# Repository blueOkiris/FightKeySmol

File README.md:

# Fight Key Smol

## Description

I made a [hitbox for myself](https://hackaday.io/project/185796-fight-key-wide) a while back that's big and has an enclosure and all that good stuff and cost me maybe $80 to make.

However, lately I've been seeing people pay well over $100 for something that should be maybe $50 max, so I'm redesigning that to fit the style people want, so there's a cheap alternative.

Now yes, you're paying for quality with the others. This doesn't come with an enclosure, and it's DIY; it's minimal, but for some people, that's worth not dropping >= $100. It's an option. That's all

So, this project aims to be a tiny, inexpensive, DIY, keyboard-based fighting-game controller.

## Software

The software included in the repo and releases is a pre-built version of the [GP2040-CE](https://github.com/OpenStickCommunity/GP2040-CE) firmware.

For version 1, there is a custom version due to Start and Select being switched. For version 2, this is not the case, and the stock software can be used.

## Parts

The only thing you need to source yourself are the key caps. You can get a cheap set for $2 on [Aliexpress](CapLink).

Beyond that, you'll want to use [Jlcpcb](https://jlcpcb.com) to order the board and use automatic assembly. This will place all the internals as well as the switches into the PCB and ship it to you.

Cost comes out to:

| Part                                              | Cost |
|:-------------------------------------------------:|:----:|
| PCB and Assembly                                  | $22  |
| PCB Shipping (Choose Global Standard for cheaper) | $10  |
| Key Caps                                          | $2   |
| Total                                             | $34  |

[CapLink]: https://www.aliexpress.us/item/3256803462871478.html?spm=a2g0o.productlist.main.15.fd98sl21sl21Ub&algo_pvid=9ed2559f-ab14-4ea8-b05c-93050b38520c&algo_exp_id=9ed2559f-ab14-4ea8-b05c-93050b38520c-7&pdp_npi=3%40dis%21USD%211.5%211.12%21%21%21%21%21%4021224e9b16806567975486574d074d%2112000026645768333%21sea%21US%210&curPageLogUid=vViLogs9j2Z2 "Aliexpress"

## Subdirectories

- pcb - Fight Key Smol KiCAD PCB project
- pics - Pics used for the README

## Ordering and Programming

1. Go to JLCPCB and click on "Instant Quote"
   
2. Click "Upload" and upload the "FightKeySmol-Gerber.zip" file from the GitHub Releases. You don't need to mess with any options here.
3. Scroll down to "PCB Assembly" and enable it. Select just one and click Submit
   
4. Click Next and then upload the "pcb/parts/BOM.xls" for the BOM and "pcb/parts/FightKey-CPL.xlsx" for the CPL. Then click process.
   
5. Click to continue on the next page, and proceed to ordering the boards.
6. Once you have the board, you need to program it. You don't need to rebuild the code or anything.
   1. Press the pico's button down and plug it in to make it show up as a drive
   2. Copy the .uf2 file in the repo to the drive. It will unmount and program and auto-remount as a controller
   
7. Enjoy!

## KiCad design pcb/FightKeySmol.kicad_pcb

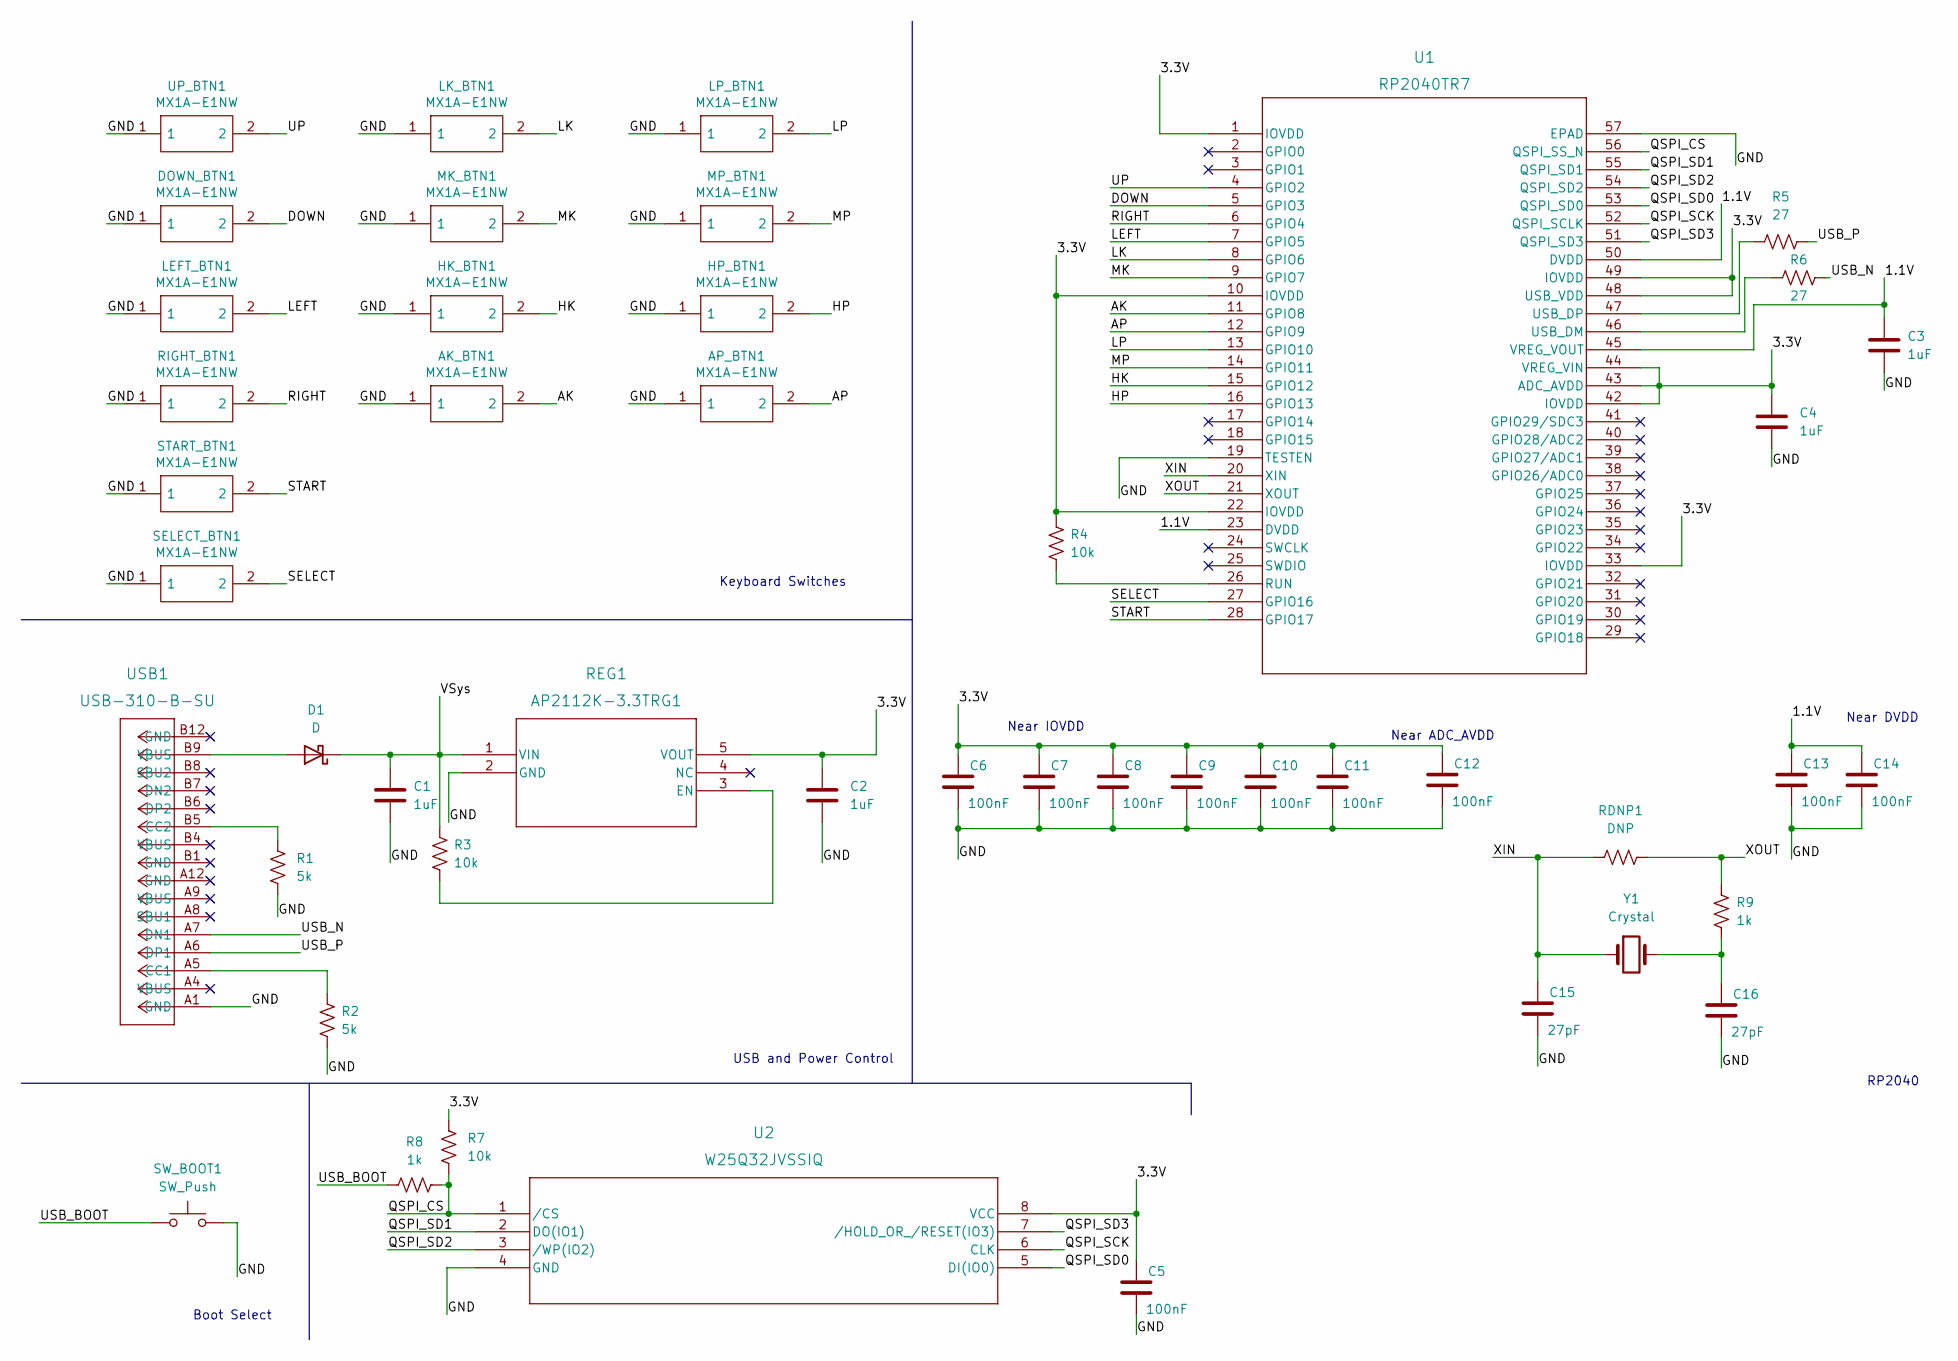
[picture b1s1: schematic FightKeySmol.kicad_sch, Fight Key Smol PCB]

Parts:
AK_BTN1: MX1A-E1NW; MX1AE1NW; Mouser Part Number 540-MX1A-E1NW
AP_BTN1: MX1A-E1NW; MX1AE1NW; Mouser Part Number 540-MX1A-E1NW
C1, C2, C3, C4: 1uF; C_0201_0603Metric
C5, C6, C7, C8, C9, C10, C11, C12, C13, C14: 100nF; C_0201_0603Metric
C15, C16: 27pF; C_0201_0603Metric
D1: D; D_SOD-323
DOWN_BTN1: MX1A-E1NW; MX1AE1NW; Mouser Part Number 540-MX1A-E1NW
HK_BTN1: MX1A-E1NW; MX1AE1NW; Mouser Part Number 540-MX1A-E1NW
HP_BTN1: MX1A-E1NW; MX1AE1NW; Mouser Part Number 540-MX1A-E1NW
LEFT_BTN1: MX1A-E1NW; MX1AE1NW; Mouser Part Number 540-MX1A-E1NW
LK_BTN1: MX1A-E1NW; MX1AE1NW; Mouser Part Number 540-MX1A-E1NW
LP_BTN1: MX1A-E1NW; MX1AE1NW; Mouser Part Number 540-MX1A-E1NW
MK_BTN1: MX1A-E1NW; MX1AE1NW; Mouser Part Number 540-MX1A-E1NW
MP_BTN1: MX1A-E1NW; MX1AE1NW; Mouser Part Number 540-MX1A-E1NW
R1, R2: 5k; R_0805_2012Metric
R3, R4, R7: 10k; R_0201_0603Metric
R5, R6: 27; R_0201_0603Metric
R8, R9: 1k; R_0201_0603Metric
RDNP1: DNP; R_0201_0603Metric
REG1: AP2112K-3.3TRG1; SOT_RG1_DIO
RIGHT_BTN1: MX1A-E1NW; MX1AE1NW; Mouser Part Number 540-MX1A-E1NW
SELECT_BTN1: MX1A-E1NW; MX1AE1NW; Mouser Part Number 540-MX1A-E1NW
START_BTN1: MX1A-E1NW; MX1AE1NW; Mouser Part Number 540-MX1A-E1NW
SW_BOOT1: SW_Push; SW_SPST_PTS645
U1: RP2040TR7; RP2040TR7_RPI
U2: W25Q32JVSSIQ; SOIC-8_5P28X5P28_WIN
UP_BTN1: MX1A-E1NW; MX1AE1NW; Mouser Part Number 540-MX1A-E1NW
USB1: USB-310-B-SU; CONN_USB-310-B-SU_HYA
Y1: Crystal; Crystal_SMD_HC49-SD

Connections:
/1.1V: C3.1, C13.1, C14.1, U1.23 (DVDD), U1.45 (VREG_VOUT), U1.50 (DVDD)
/3.3V: C2.1, C4.1, C5.1, C6.1, C7.1, C8.1, C9.1, C10.1, C11.1, C12.1, R4.1, R7.1, REG1.5 (VOUT), U1.1 (IOVDD), U1.10 (IOVDD), U1.22 (IOVDD), U1.33 (IOVDD), U1.42 (IOVDD), U1.43 (ADC_AVDD), U1.44 (VREG_VIN), U1.48 (USB_VDD), U1.49 (IOVDD), U2.8 (VCC)
/AK: AK_BTN1.2, U1.11 (GPIO8)
/AP: AP_BTN1.2, U1.12 (GPIO9)
/DOWN: DOWN_BTN1.2, U1.5 (GPIO3)
/GND: AK_BTN1.1, AP_BTN1.1, C1.2, C2.2, C3.2, C4.2, C5.2, C6.2, C7.2, C8.2, C9.2, C10.2, C11.2, C12.2, C13.2, C14.2, C15.2, C16.2, DOWN_BTN1.1, HK_BTN1.1, HP_BTN1.1, LEFT_BTN1.1, LK_BTN1.1, LP_BTN1.1, MK_BTN1.1, MP_BTN1.1, R1.2, R2.2, REG1.2 (GND), RIGHT_BTN1.1, SELECT_BTN1.1, START_BTN1.1, SW_BOOT1.2, U1.19 (TESTEN), U1.57 (EPAD), U2.4 (GND), UP_BTN1.1, USB1.A1 (GND)
/HK: HK_BTN1.2, U1.15 (GPIO12)
/HP: HP_BTN1.2, U1.16 (GPIO13)
/LEFT: LEFT_BTN1.2, U1.7 (GPIO5)
/LK: LK_BTN1.2, U1.8 (GPIO6)
/LP: LP_BTN1.2, U1.13 (GPIO10)
/MK: MK_BTN1.2, U1.9 (GPIO7)
/MP: MP_BTN1.2, U1.14 (GPIO11)
/QSPI_CS: R7.2, R8.2, U1.56 (QSPI_SS_N), U2.1 (/CS)
/QSPI_SCK: U1.52 (QSPI_SCLK), U2.6 (CLK)
/QSPI_SD0: U1.53 (QSPI_SD0), U2.5 (DI(IO0))
/QSPI_SD1: U1.55 (QSPI_SD1), U2.2 (DO(IO1))
/QSPI_SD2: U1.54 (QSPI_SD2), U2.3 (/WP(IO2))
/QSPI_SD3: U1.51 (QSPI_SD3), U2.7 (/HOLD_OR_/RESET(IO3))
/RIGHT: RIGHT_BTN1.2, U1.6 (GPIO4)
/SELECT: SELECT_BTN1.2, U1.27 (GPIO16)
/START: START_BTN1.2, U1.28 (GPIO17)
/UP: U1.4 (GPIO2), UP_BTN1.2
/USB_BOOT: R8.1, SW_BOOT1.1
/USB_N: R6.1, USB1.A7 (DN1)
/USB_P: R5.2, USB1.A6 (DP1)
/VSys: C1.1, D1.1 (K), R3.1, REG1.1 (VIN)
/XIN: C15.1, RDNP1.1, U1.20 (XIN), Y1.1
/XOUT: R9.2, RDNP1.2, U1.21 (XOUT)
unnamed: C16.1, R9.1, Y1.2
unnamed: D1.2 (A), USB1.B9 (VBUS)
unnamed: R1.1, USB1.B5 (CC2)
unnamed: R2.1, USB1.A5 (CC1)
unnamed: R3.2, REG1.3 (EN)
unnamed: R4.2, U1.26 (RUN)
unnamed: R5.1, U1.47 (USB_DP)
unnamed: R6.2, U1.46 (USB_DM)

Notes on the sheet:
Near ADC_AVDD
Boot Select
Near DVDD
Near IOVDD
RP2040
USB and Power Control
Keyboard Switches

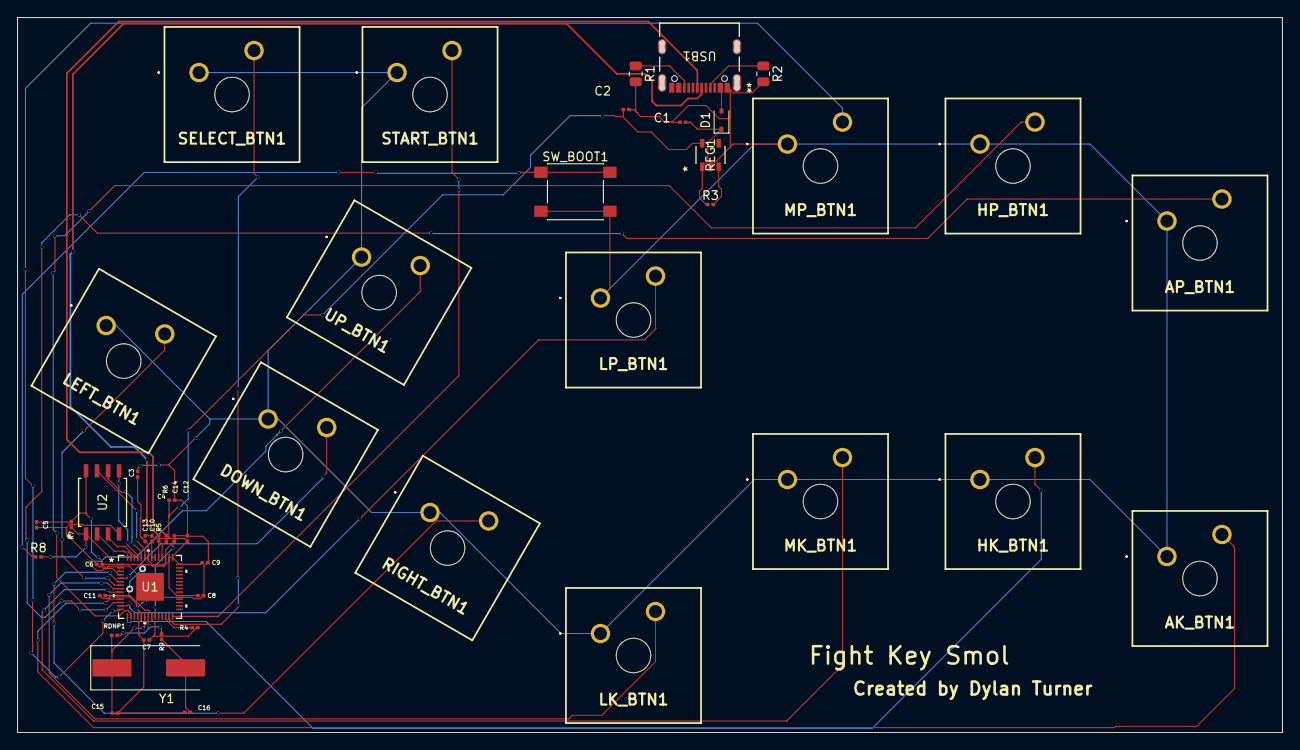
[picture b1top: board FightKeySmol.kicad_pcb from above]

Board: 2 copper layers, 146.1 x 82.6 mm, 47 parts (0 on the bottom side), 37 nets.

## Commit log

2023-04-05 pcb: added from fightkey-wide proj
2023-04-05 README: initial template with basic motivations
2023-04-05 README: update tag line
2023-04-05 GP2040-CE: added code for programming
2023-04-05 README: add disclaimer about project state
2023-04-05 LICENSE: added MIT (what GP2040-CE uses)
    I don't care all that much, since I'm not doing any coding
2023-04-05 gitignore: ignore KiCAD output/backup files
2023-04-05 README: switches link points to cheap knockoffs
    No need for fancy ones since this is a low-end device
2023-04-05 kicad_sch: redesigned to use input_pullup
    This is the standard for GP2040 style sticks.
    Use PICO_BOARD_CONFIG_H_
2023-04-05 kicad_sch: added second ground on other side
2023-04-05 kicad_pcb: updated for schem and new tiny design
2023-04-05 kicad_pcb: updated for new design
2023-04-05 README: note programming in build steps
2023-04-05 jlcpcb-order: pic of options
2023-04-05 README: update cost
2023-04-05 README: found cheaper alternatives
2023-04-05 README: update expected
2023-04-14 GP2040-CE_0.6.2_Pico: added fk program
2023-04-14 GP2040-CE_0.6.2_Pico: switched start/select
    I mixed up S1 and S2 when designing the PCB
2023-04-14 pics/: added build pics
2023-04-14 README: updated build steps for "release"
    I.e. initial version is ready, and I can fill in the build steps
2023-04-14 GP2040-CE: switched to custom version
2023-04-14 README: fix typo
2023-04-14 README: update links and costs
2023-04-14 README: noted use of hot glue as feet alternative
2023-04-14 README: noted pics folder
2023-04-14 README: fixed cost note
2023-04-14 kicad_pcb: shrink board; switch start sel
2023-04-14 kicad_sch: switch start/sel
2023-04-14 gitmodules: remove uneeded fork of GP2040
2023-04-14 GP2040-CE: replaced with stock
2023-04-14 kicad_sch: delete pico
2023-04-14 kicad_pcb: delete pico, rm traces, shrink board
2023-04-14 README: add info on GP2040-CE
2023-04-14 USB-310-B: usb-C connector for custom board
2023-04-14 BOM: initialized BOM with USB-C
2023-04-14 pico-soldering: removed
    Built-in board with through hole, but not pico
2023-04-14 README: add flash chip to cost
2023-04-14 ul_W25Q32JVSSIQ: flash chip added
2023-04-14 BOM: add voltage regulator
2023-04-14 ul_AP2112K-3.3TRG1: voltage regulator
2023-04-14 BOM: resistors for USB-C power
2023-04-14 fp-lib-table: add parts to project symbol lib
2023-04-14 sym-lib-table: add custom parts to sym lib
2023-04-14 fp-info-cache: updated resistor footprints
2023-04-14 kicad_sch: implement USB/Power circuit
2023-04-14 kicad_pcb: place and route parts for USB/Power
2023-04-14 kicad_pro: new parts
2023-04-14 BOM: updated for power circuitry
2023-04-15 ul_RP2040TR7: 2040 symbols/footprint library
2023-04-15 fp-lib-table: add 2040 library
2023-04-15 sym-lib-table: add 2040 symbol lib
2023-04-15 kicad_sch: set up 2040 circuit
2023-04-15 BOM: completed (unless errors)
2023-04-15 kicad_*: finished implementing custom 2040 circuit
    Should work and should be able to be placed entirely by manufacturer
2023-04-15 BOM: updated parts to be easier to place
2023-04-15 CPL: parts placement file
2023-04-15 GP2040: remove since stock
    It can just go under "Releases"
2023-04-15 pics: remove old build pics
    Irrelevant now
2023-04-15 drag-n-drop: readded bc still relevant
2023-04-15 README: rough draft of new build instructions
2023-04-17 BOM: switch part to one with more stock
    Signed-of-by: Dylan Turner <dylantdmt@gmail.com>
2023-04-17 BOM and CPL: removed Switches
    Not cost effective
